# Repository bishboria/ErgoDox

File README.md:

# Information

My colemak layout (without `teensy button`) http://configure.ergodox-ez.com/keyboard_layouts/qajjmk/edit 

I aim for symmetry of modifier keys, primarily: I get Emacs Pinky quite quickly when using a standard (1 ctrl button) laptop keyboard.

## Updating the keyboard layout

Use ErgoDox EZ configurator (with my layout as the basis): http://configure.ergodox-ez.com/keyboard_layouts/qajjmk/edit

This great configurator has loads of extra keys that I had to add manually, and painfully, to a `C` file.

## Updating keyboard layout

* Run teensy.app from teensy.dmg
* Press +L1 then teensy button (on the old layout, EZ layout configurator doesn't have this `teensy button`)
* Open newest .hex file
* Program
* Reboot

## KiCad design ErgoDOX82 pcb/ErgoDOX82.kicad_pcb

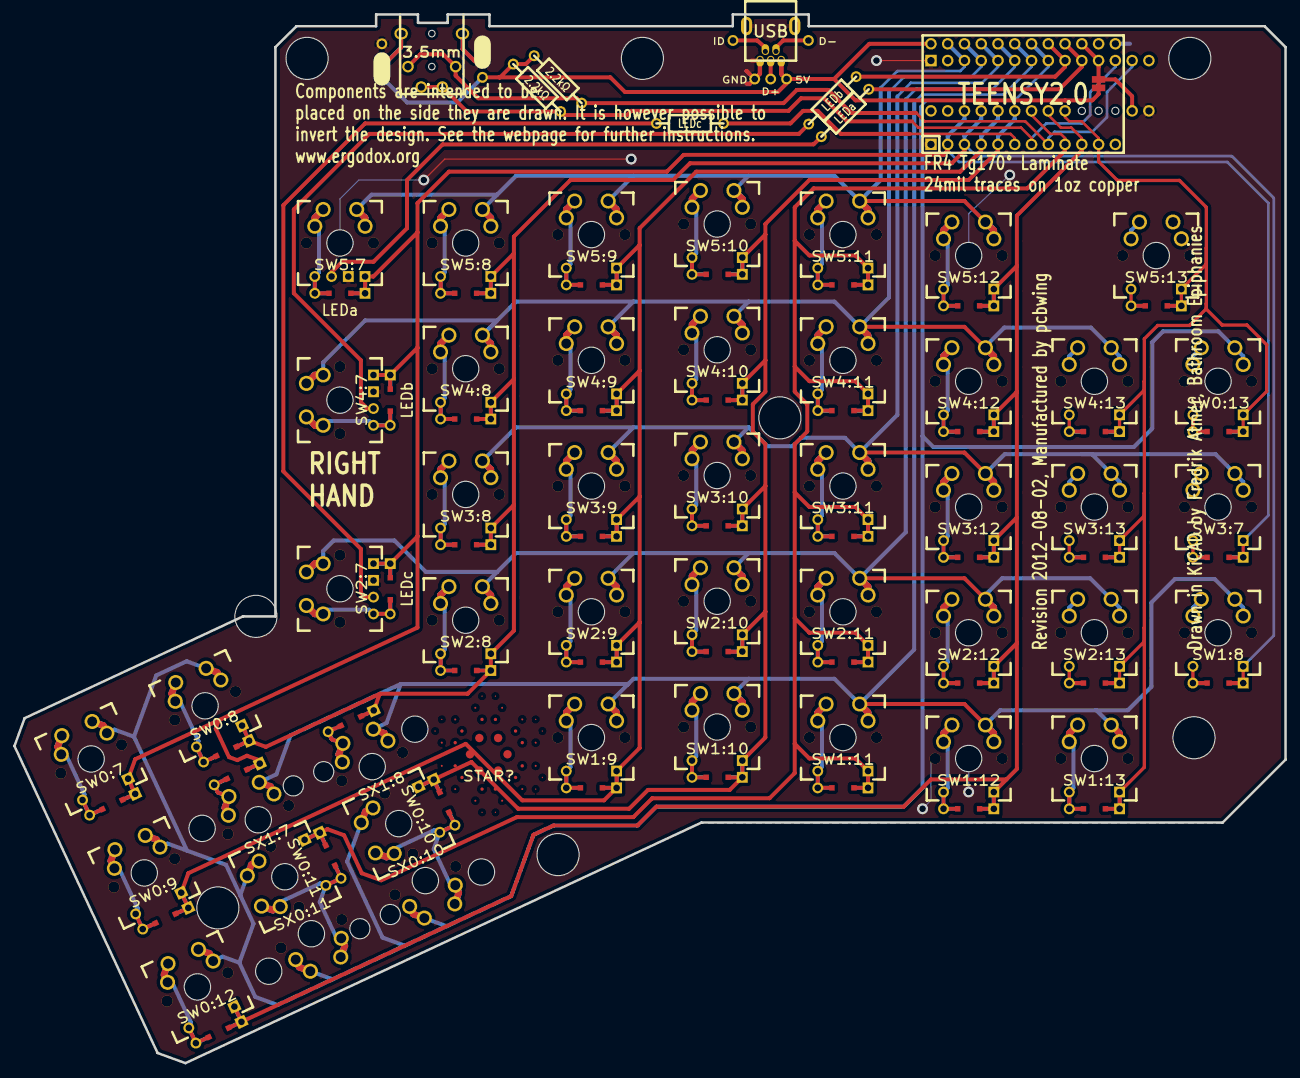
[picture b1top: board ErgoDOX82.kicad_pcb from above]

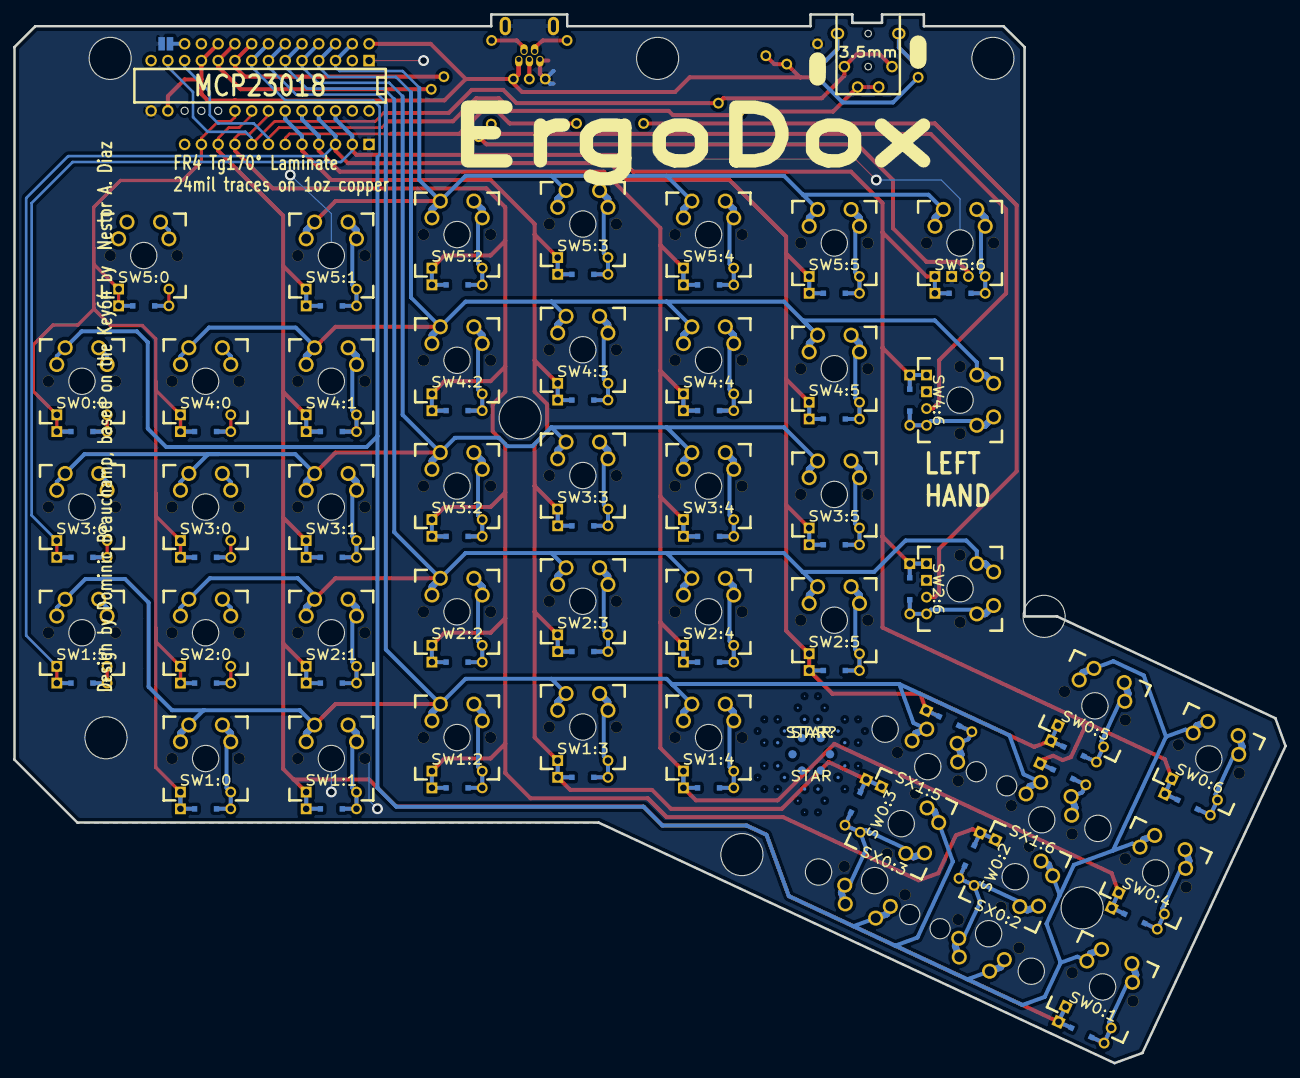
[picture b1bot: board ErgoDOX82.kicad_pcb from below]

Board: 2 copper layers, 192.6 x 158.9 mm, 68 parts (4 on the bottom side), 60 nets.

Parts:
D1:7, D1:8: D; DIODE
H99: MECHANICAL; ErgoDOXmech
J1: USB; USBMINImod
J2: 3.5mm; 4pin35mmAudio
J3, J4: JMP; 100PITCH1X3
JP1, JP2: JUMPER; GAP
LED_A1: LEDa; MX_LED
LED_B1: LEDb; MX_LED
LED_C1: LEDc; MX_LED
R1, R2: 2.2kΩ; RESISTOR
RA1: LEDa; RESISTOR
RB1: LEDb; RESISTOR
RC1: LEDc; RESISTOR
S1, S2: STAB200; STAB_PCB940
STAR?: STAR
STAR?#2: STAR
SW0:7: SW0:6; MX_FLIP_DIODE
SW0:8: SW0:5; MX_FLIP_DIODE
SW0:9: SW0:4; MX_FLIP_DIODE
SW0:10: SW0:3; MX_FLIP_DIODE
SW0:11: SW0:2; MX_FLIP_DIODE
SW0:12: SW0:1; MX_FLIP_DIODE
SW0:13: SW0:0; MX_FLIP_DIODE
SW1:8: SW1:5; MX_FLIP_DIODE
SW1:9: SW1:4; MX_FLIP_DIODE
SW1:10: SW1:3; MX_FLIP_DIODE
SW1:11: SW1:2; MX_FLIP_DIODE
SW1:12: SW1:1; MX_FLIP_DIODE
SW1:13: SW1:0; MX_FLIP_DIODE
SW2:7: SW2:6; MX_FLIP_DIODE
SW2:8: SW2:5; MX_FLIP_DIODE
SW2:9: SW2:4; MX_FLIP_DIODE
SW2:10: SW2:3; MX_FLIP_DIODE
SW2:11: SW2:2; MX_FLIP_DIODE
SW2:12: SW2:1; MX_FLIP_DIODE
SW2:13: SW2:0; MX_FLIP_DIODE
SW3:7: SW3:6; MX_FLIP_DIODE
SW3:8: SW3:5; MX_FLIP_DIODE
SW3:9: SW3:4; MX_FLIP_DIODE
SW3:10: SW3:3; MX_FLIP_DIODE
SW3:11: SW3:2; MX_FLIP_DIODE
SW3:12: SW3:1; MX_FLIP_DIODE
SW3:13: SW3:0; MX_FLIP_DIODE
SW4:7: SW4:6; MX_FLIP_DIODE
SW4:8: SW4:5; MX_FLIP_DIODE
SW4:9: SW4:4; MX_FLIP_DIODE
SW4:10: SW4:3; MX_FLIP_DIODE
SW4:11: SW4:2; MX_FLIP_DIODE
SW4:12: SW4:1; MX_FLIP_DIODE
SW4:13: SW4:0; MX_FLIP_DIODE
SW5:7: SW5:6; MX_FLIP_DIODE
SW5:8: SW5:5; MX_FLIP_DIODE
SW5:9: SW5:4; MX_FLIP_DIODE
SW5:10: SW5:3; MX_FLIP_DIODE
SW5:11: SW5:2; MX_FLIP_DIODE
SW5:12: SW5:1; MX_FLIP_DIODE
SW5:13: SW5:0; MX_FLIP_DIODE
SX0:10: SX0:3; MX_FLIP
SX0:11: SX0:2; MX_FLIP
SX1:7: SX1:6; MX_FLIP
SX1:8: SX1:5; MX_FLIP
U1: TEENSY2.0; TEENSY_2.0
U2: MCP23018; DIP28_300

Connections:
/COL0: SW0:13.4, SW1:13.4, SW2:13.4, SW3:13.4, SW4:13.4, SW5:13.4, U1.11, U2.20
/COL1: SW0:12.4, SW1:12.4, SW2:12.4, SW3:12.4, SW4:12.4, SW5:12.4, U1.10, U2.21
/COL4: SW0:9.4, SW1:9.4, SW2:9.4, SW3:9.4, SW4:9.4, SW5:9.4, U1.4, U2.24
/COL5: D1:8.2, SW0:8.4, SW1:8.4, SW2:8.4, SW3:8.4, SW4:8.4, SW5:8.4, U1.3, U2.25
/COL6: D1:7.2, SW0:7.4, SW2:7.4, SW3:7.4, SW4:7.4, SW5:7.4, U1.2, U2.26
/COL10: SW0:10.4, SW1:10.4, SW2:10.4, SW3:10.4, SW4:10.4, SW5:10.4, U1.5, U2.23
/COL11: SW0:11.4, SW1:11.4, SW2:11.4, SW3:11.4, SW4:11.4, SW5:11.4, U1.9, U2.22
/LED_A: RA1.1, U1.21
/LED_B: RB1.1, U1.22
/LED_C: RC1.1, U1.6
/ROW0: SW0:7.1, SW0:8.1, SW0:9.1, SW0:10.1, SW0:11.1, SW0:12.1, SW0:13.1, SX0:10.1, SX0:11.1, U1.23, U2.8
/ROW1: SW1:8.1, SW1:9.1, SW1:10.1, SW1:11.1, SW1:12.1, SW1:13.1, SX1:7.1, SX1:8.1, U1.24, U2.7
/ROW2: SW2:7.1, SW2:8.1, SW2:9.1, SW2:10.1, SW2:11.1, SW2:12.1, SW2:13.1, U1.25, U2.6
/ROW3: SW3:7.1, SW3:8.1, SW3:9.1, SW3:10.1, SW3:11.1, SW3:12.1, SW3:13.1, U1.26, U2.5
/ROW4: SW4:7.1, SW4:8.1, SW4:9.1, SW4:10.1, SW4:11.1, SW4:12.1, SW4:13.1, U1.27, U2.4
/ROW5: SW5:7.1, SW5:8.1, SW5:9.1, SW5:10.1, SW5:11.1, SW5:12.1, SW5:13.1, U1.28, U2.3
/SCLM: J2.3, J2.5, R2.2, U1.7, U2.12
/SDAM: J2.2, J2.6, R1.2, U1.8, U2.13
GND: H99.0, J1.5, J1.6, J3.3, J4.3, JP2.1, LED_A1.2, LED_B1.2, LED_C1.2, S1.0, S2.0, SW0:7.0, SW0:8.0, SW0:9.0, SW0:10.0, SW0:11.0, SW0:12.0, SW0:13.0, SW1:8.0, SW1:9.0, SW1:10.0, SW1:11.0, SW1:12.0, SW1:13.0, SW2:7.0, SW2:8.0, SW2:9.0, SW2:10.0, SW2:11.0, SW2:12.0, SW2:13.0, SW3:7.0, SW3:8.0, SW3:9.0, SW3:10.0, SW3:11.0, SW3:12.0, SW3:13.0, SW4:7.0, SW4:8.0, SW4:9.0, SW4:10.0, SW4:11.0, SW4:12.0, SW4:13.0, SW5:7.0, SW5:8.0, SW5:9.0, SW5:10.0, SW5:11.0, SW5:12.0, SW5:13.0, SX0:10.0, SX0:11.0, SX1:7.0, SX1:8.0, U1.1, U1.18, U2.1, U2.15
unnamed: D1:7.1, SX1:7.2
unnamed: J2.1, J3.2
unnamed: J2.4, J4.2
unnamed: LED_A1.1, RA1.2
unnamed: LED_B1.1, RB1.2
unnamed: LED_C1.1, RC1.2
unnamed: SW0:7.2, SW0:7.3
unnamed: SW0:8.2, SW0:8.3
unnamed: SW0:9.2, SW0:9.3
unnamed: SW0:10.2, SW0:10.3, SX0:10.2
unnamed: SW0:11.2, SW0:11.3, SX0:11.2
unnamed: SW0:12.2, SW0:12.3
unnamed: SW1:9.2, SW1:9.3
unnamed: SW1:10.2, SW1:10.3
unnamed: SW1:11.2, SW1:11.3
unnamed: SW1:12.2, SW1:12.3
unnamed: SW1:13.2, SW1:13.3
unnamed: SW2:7.2, SW2:7.3
unnamed: SW2:8.2, SW2:8.3
unnamed: SW2:9.2, SW2:9.3
unnamed: SW2:10.2, SW2:10.3
unnamed: SW2:11.2, SW2:11.3
unnamed: SW1:8.2, SW1:8.3, SW2:12.2, SW2:12.3, SW2:13.2, SW2:13.3
unnamed: SW3:8.2, SW3:8.3
unnamed: SW3:9.2, SW3:9.3
unnamed: SW3:10.2, SW3:10.3
unnamed: SW3:11.2, SW3:11.3
unnamed: SW3:7.2, SW3:7.3, SW3:12.2, SW3:12.3, SW3:13.2, SW3:13.3
unnamed: SW4:7.2, SW4:7.3
unnamed: SW4:8.2, SW4:8.3
unnamed: SW4:9.2, SW4:9.3
unnamed: SW4:10.2, SW4:10.3
unnamed: SW4:11.2, SW4:11.3
unnamed: SW0:13.2, SW0:13.3, SW4:12.2, SW4:12.3, SW4:13.2, SW4:13.3
unnamed: SW5:7.2, SW5:7.3
unnamed: SW5:8.2, SW5:8.3
unnamed: SW5:9.2, SW5:9.3
unnamed: SW5:10.2, SW5:10.3
unnamed: SW5:11.2, SW5:11.3
unnamed: SW5:12.2, SW5:12.3, SW5:13.2, SW5:13.3
VCC: J1.1, J3.1, J4.1, JP1.1, R1.1, R2.1, U1.20, U1.29, U2.11, U2.16

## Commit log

2013-07-07 Keyboard configuration and how to update it.
2014-03-04 Layout now has media keys working: play/pause, next, previous
    See https://github.com/bishboria/ergodox-firmware/blob/master/src/keyboard/ergodox/layout/custom-colemak.c for details of where the keys are.
2014-03-04 Add link to key layout in readme
2014-12-31 Remove unnecessary space in file names
2014-12-31 Cleanup dxf files so they more suited for laser cutting
    These changes have been applied:
    - duplicated lines have been removed
    - random dots have been removed
    - lines have been combined into a polyline
2015-10-12 Measurement data is missing from the `.dxf` files
    I was contacted by email by someone trying to acquire the parts individually (something I haven't done) and the measurements for acrylic layer thickness are missing.
    Got old fashioned and used a ruler.
2016-07-06 new ergodox 82
2016-07-06 modified to ergodox 82
    Ergodox 82 に対応
2016-07-28 Revert "modified to ergodox 82"
    This reverts commit b3812b70bbacd4e88ae3806a416e84006052be05.
2016-10-07 EZ configurator generated hex file
    Using the lovely ergodox EZ configurator, I remade my layout:
    Clone&modify or download from here: http://configure.ergodox-ez.com/keyboard_layouts/qajjmk
2016-10-07 Pointing to new EZ configurator
2016-12-02 Bug fixes
    Outer layer switch fix - clean up pcb (Holes from GND->Hole) - Update silkscreen
2016-12-02 Update gerbers to match updated kicad files
